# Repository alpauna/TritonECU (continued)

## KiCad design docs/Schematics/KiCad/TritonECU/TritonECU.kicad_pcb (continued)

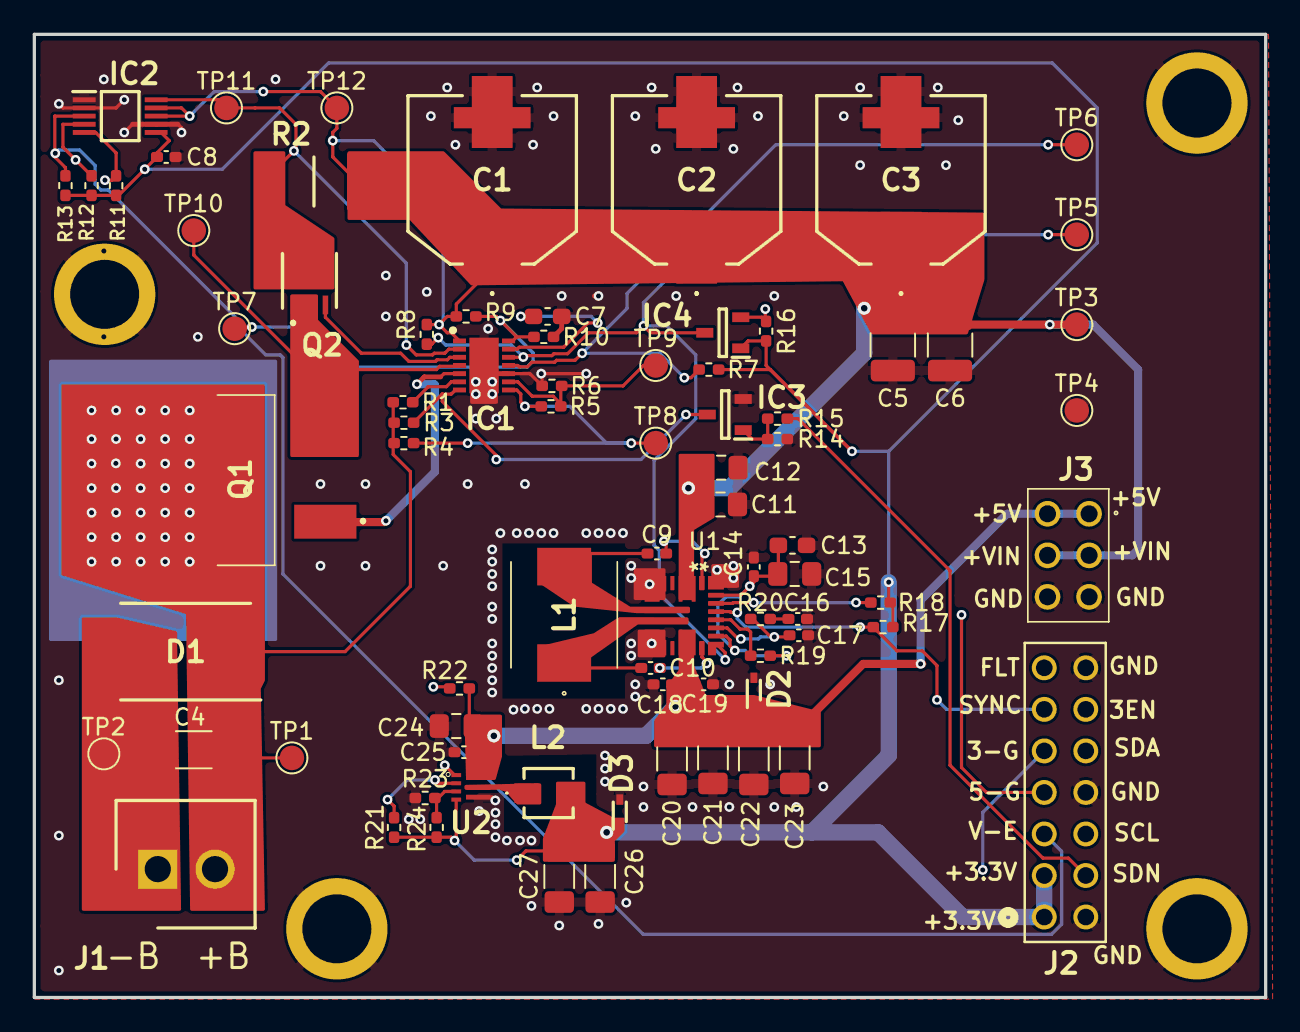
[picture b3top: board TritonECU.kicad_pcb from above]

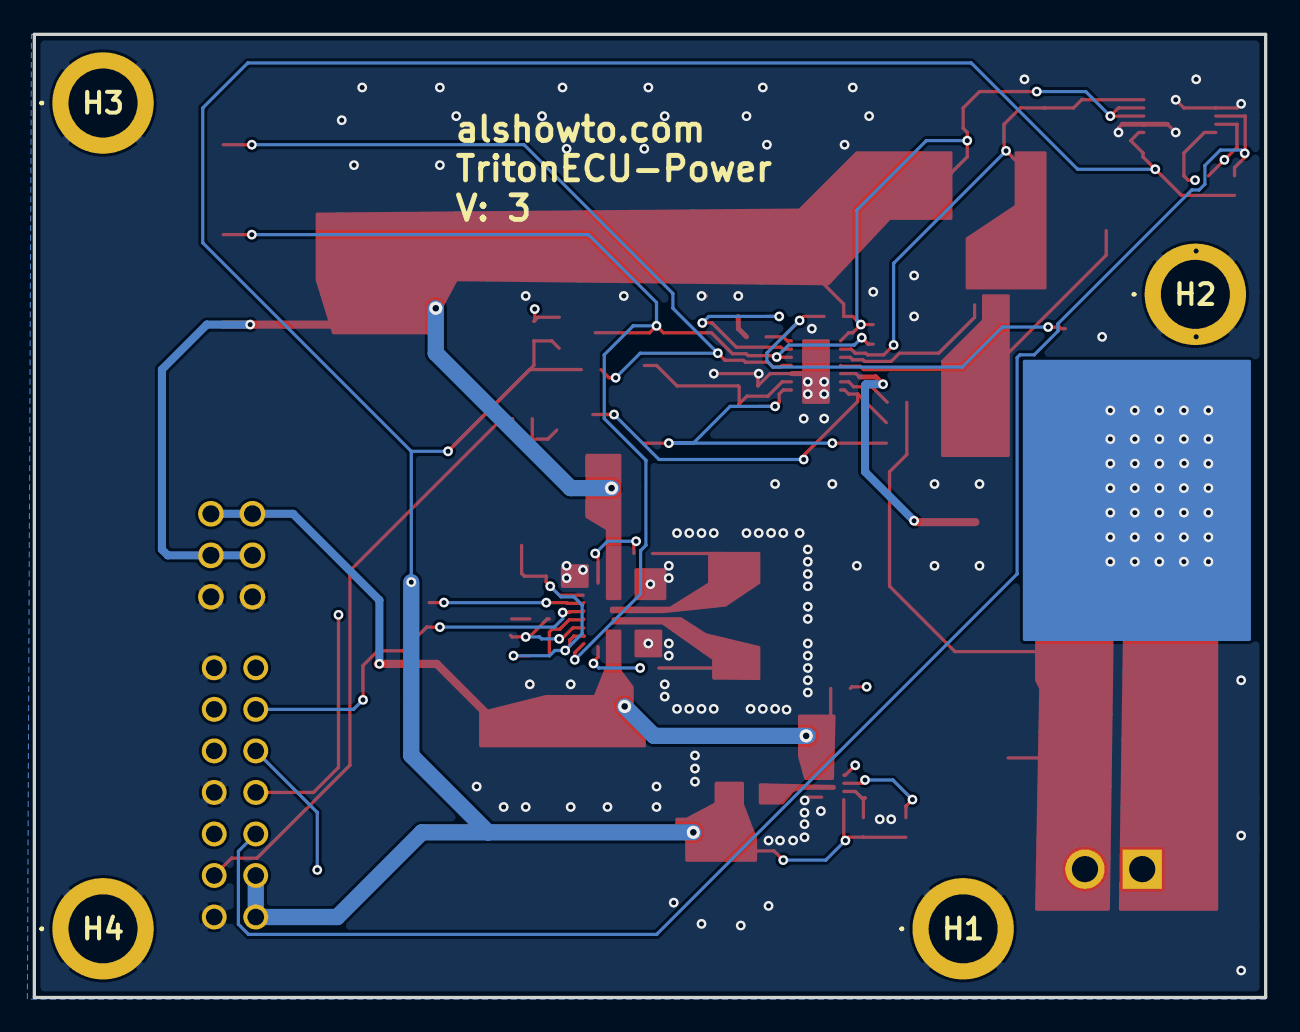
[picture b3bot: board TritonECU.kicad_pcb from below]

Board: 4 copper layers, 75.3 x 58.9 mm, 83 parts (4 on the bottom side), 38 nets.

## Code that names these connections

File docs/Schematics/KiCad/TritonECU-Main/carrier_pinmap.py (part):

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import mcu_pinout as mp

# Standby wake-up pins (DS11532 / RM0410 PWR_CSR2); PI8/PI11 are not on LQFP144
WKUP = {'PA0': 'WKUP1', 'PA2': 'WKUP2', 'PC1': 'WKUP3', 'PC13': 'WKUP4'}
RESERVED = {'PA13': 'SWDIO (STDC14)', 'PA14': 'SWCLK (STDC14)', 'PB3': 'SWO (STDC14)',
            'PD8': 'USART3 TX, ST-Link VCP (STDC14)', 'PD9': 'USART3 RX, ST-Link VCP (STDC14)'}

# Timer modes. 'sched': free-running counter, output compare / input capture at
# arbitrary times. 'pwm': fixed period, the channels share it.
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#   or 'GPIO'.
SIGNALS = [
    # --- ignition: 8 x COP, 74HCT541 #1 -> ISL9V3040. Cylinder numbers.
    ('COIL1', 'PD12', 'TIM4_CH1', False, 'ignition', ''),
    ('COIL2', 'PD13', 'TIM4_CH2', False, 'ignition', ''),
    ('COIL3', 'PD14', 'TIM4_CH3', False, 'ignition', ''),
    ('COIL4', 'PD15', 'TIM4_CH4', False, 'ignition', ''),
    ('COIL5', 'PC6',  'TIM8_CH1', False, 'ignition', ''),
    ('COIL6', 'PC7',  'TIM8_CH2', False, 'ignition', ''),
    ('COIL7', 'PC8',  'TIM8_CH3', False, 'ignition', ''),
    ('COIL8', 'PC9',  'TIM8_CH4', False, 'ignition', ''),
    ('COIL_ARM', 'PD11', 'GPIO', False, 'ignition', '74HCT541 #1 OE1: engine position known, ignition armed'),
    ('WDI', 'PD10', 'GPIO', False, 'ignition', 'TPS3823A-33 kick; its RESET drives OE2 of #1 and OE of #3. NO pull resistor'),
    # --- injection: 8 x ZXMS6005DGQ, direct
    ('INJ1', 'PE9',  'TIM1_CH1', False, 'injection', ''),
    ('INJ2', 'PE11', 'TIM1_CH2', False, 'injection', ''),
    ('INJ3', 'PE13', 'TIM1_CH3', False, 'injection', ''),
    ('INJ4', 'PE14', 'TIM1_CH4', False, 'injection', ''),
    ('INJ5', 'PB4',  'TIM3_CH1', False, 'injection', ''),
    ('INJ6', 'PB5',  'TIM3_CH2', False, 'injection', ''),
    ('INJ7', 'PB14', 'TIM12_CH1', False, 'injection', ''),
    ('INJ8', 'PB15', 'TIM12_CH2', False, 'injection', ''),
    # --- position and speed: 3 x MAX9926
    ('CKP', 'PA15', 'TIM2_CH1', False, 'vr', '36-1 crank; capture on the 32-bit TIM2 timebase'),
    ('CMP', 'PB10', 'TIM2_CH3', False, 'vr', 'cam; capture on TIM2'),
    ('OSS', 'PB6', 'GPIO', True, 'vr', 'output shaft; EXTI + timestamp'),
    ('TSS', 'PB7', 'GPIO', True, 'vr', 'turbine shaft, pin 59; EXTI + timestamp'),
    ('TC_SPEED', 'PE0', 'GPIO', True, 'vr', 'transfer case, pin 7; EXTI + timestamp'),
    # --- ADS8588H, SPI3
    ('ADC_SCK', 'PC10', 'SPI3_SCLK', False, 'adc', ''),
    ('ADC_MISO', 'PC11', 'SPI3_MISO', False, 'adc', 'DOUTA'),
    ('ADC_CS', 'PD2', 'GPIO', False, 'adc', 'software chip select'),
    ('ADC_CONVST', 'PB11', 'TIM2_CH4', False, 'adc', 'CONVSTA+B; compare output on the crank timebase'),
    ('ADC_BUSY', 'PD3', 'GPIO', True, 'adc', 'falling edge = data ready'),
    ('ADC_RESET', 'PD4', 'GPIO', False, 'adc', 'active high; OS0-2, RANGE strapped, FRSTDATA not wired'),
    ('ADC_REF_EN', 'PG10', 'GPIO', False, 'adc', 'MAX6070AAUT25 EN, 10k pulldown: gated off in Standby, always-on-domain.md'),
    # --- internal ADC, analog (3.3 V full scale)
    ('KNOCK', 'PC3', 'ADC1', False, 'analog', '200 kSPS on ADC1, adc-front-end.md'),
    ('DPFE', 'PF3', 'ADC', False, 'analog', ''),
    ('TFT', 'PF4', 'ADC', False, 'analog', 'tft-sensor.md'),
    ('O2_DN1', 'PF6', 'ADC', False, 'analog', 'HO2S #12, buffered'),
    ('O2_DN2', 'PF7', 'ADC', False, 'analog', 'HO2S #22, buffered'),
    ('FP_MON', 'PF10', 'ADC', False, 'analog', 'fuel pump monitor'),
    ('TR3A', 'PC0', 'ADC', False, 'analog', 'three-state, 4R100 270R; 4r100-deltas.md'),
    ('VREF_CS', 'PC1', 'ADC', False, 'analog', 'TPS2H160B current sense, via 4.7k + Schottky'),
    ('VREF_STB', 'PC2', 'ADC', False, 'analog', 'VREF feed short-to-battery divider'),
    ('MUX_OUT', 'PA2', 'ADC', False, 'analog', '74HC4051 COM: drain sense x6 (HO2S x4, EVAP, vent), supply sense 1138, 391'),
    ('MUX_S0', 'PB0', 'GPIO', False, 'analog', '74HC4051 select'),
    ('MUX_S1', 'PB1', 'GPIO', False, 'analog', '74HC4051 select'),
    ('MUX_S2', 'PA7', 'GPIO', False, 'analog', '74HC4051 select'),
    ('O2_BIAS', 'PA4', 'DAC_OUT1', False, 'analog', 'DAC -> 1k -> 455 mV bias node, o2-input-stage.md'),
    # --- solenoids and heaters: 74HCT541 #3 @ 5 V -> NCV8405A x8 (full)
    ('HTR11', 'PG2', 'GPIO', False, 'solenoid', 'HO2S #11 heater, software PWM (ramp, stagger)'),
    ('HTR21', 'PG3', 'GPIO', False, 'solenoid', 'HO2S #21 heater'),
    ('HTR12', 'PG4', 'GPIO', False, 'solenoid', 'HO2S #12 heater'),
    ('HTR22', 'PG5', 'GPIO', False, 'solenoid', 'HO2S #22 heater'),
    ('VENT', 'PG6', 'GPIO', False, 'solenoid', 'canister vent, pin 67'),
    ('IMCC', 'PG7', 'GPIO', False, 'solenoid', 'pin 46'),
    ('SSA', 'PG8', 'GPIO', False, 'solenoid', 'pin 6 (5.4L; 27 is the 4.6L pin)'),
    ('SSB', 'PB12', 'GPIO', False, 'solenoid', 'pin 11 (5.4L; 1 is the 4.6L pin)'),
    # --- PWM loads: 74HCT541 #2 @ 5 V
    ('EVAP', 'PE5', 'TIM9_CH1', False, 'pwm', 'purge, pin 56; shares TIM9 period with EGR'),
    ('EGR', 'PE6', 'TIM9_CH2', False, 'pwm', 'EVR, pin 47'),
    ('EPC', 'PB8', 'TIM10_CH1', False, 'pwm', 'NCV8408B, pin 81, >= 200 Hz, own timer'),
    ('TCC', 'PB9', 'TIM11_CH1', False, 'pwm', 'pin 54, own timer'),
    ('IAC', 'PF8', 'TIM13_CH1', False, 'pwm', 'pin 83, own timer'),
    ('VSS_OUT', 'PA3', 'TIM5_CH4', False, 'pwm', 'pin 68 open drain via NCV8405A #13; frequency by compare toggle'),
    ('CCS', 'PB13', 'GPIO', False, 'pwm', 'coast clutch, pin 20, #2 ch7'),
    ('PWM_OE', 'PA8', 'GPIO', False, 'pwm', '74HCT541 #2 OE, software-releasable'),
    # --- relays: TBD62083AFNG, direct at 3.3 V
    ('FPUMP', 'PE7', 'GPIO', False, 'relay', ''),
    ('FAN1', 'PE12', 'GPIO', False, 'relay', ''),
    ('FAN2', 'PE15', 'GPIO', False, 'relay', ''),
    ('ACC', 'PG0', 'GPIO', False, 'relay', 'A/C clutch'),
    # --- switch inputs, conditioned
    ('TR1', 'PF11', 'GPIO', True, 'input', 'pin 34'),
    ('TR2', 'PF12', 'GPIO', True, 'input', 'pin 49'),
    ('TR4', 'PF14', 'GPIO', True, 'input', 'pin 50'),
    ('BRAKE', 'PF15', 'GPIO', True, 'input', ''),
    ('ACP', 'PE10', 'GPIO', True, 'input', 'A/C pressure'),
    ('4X4L', 'PE8', 'GPIO', True, 'input', '4x4 low indicator switch, pin 14 (findings sec.14)'),
    ('TCS', 'PE1', 'GPIO', False, 'input', 'O/D cancel switch, pin 29; polled, all EXTI lines are taken'),
    # --- VREF: TPS2H160B-Q1, DIAG_EN tied high
    ('VREF_EN', 'PB2', 'GPIO', False, 'vref', ''),
    ('VREF_IN1', 'PF13', 'GPIO', False, 'vref', ''),
    ('VREF_IN2', 'PC4', 'GPIO', False, 'vref', ''),
    ('VREF_SEL', 'PC5', 'GPIO', False, 'vref', ''),
    ('VREF_FAULT', 'PF9', 'GPIO', True, 'vref', ''),
    # --- SCP / J1850 PWM: DRV8837 + TLV7031
    ('J1850_TXP', 'PG13', 'GPIO', False, 'j1850', 'same port as TXN: one BSRR write'),
    ('J1850_TXN', 'PG14', 'GPIO', False, 'j1850', ''),
    ('J1850_NSLEEP', 'PG15', 'GPIO', False, 'j1850', ''),
    ('J1850_RX', 'PA1', 'TIM2_CH2', False, 'j1850', 'capture on the TIM2 timebase'),
    # --- CAN: TJA1042T/3
    ('CAN_RX', 'PD0', 'CAN1_CAN_RD', False, 'can', ''),
    ('CAN_TX', 'PD1', 'CAN1_CAN_TD', False, 'can', ''),
    ('CAN_STB', 'PD5', 'GPIO', False, 'can', 'not strapped: standby is what reaches 20 uA'),
    ('CAN_RX_WAKE', 'PA0', 'WKUP1', False, 'can', 'SAME NET as CAN_RX: Standby wakes only on a WKUP pin'),
    # --- wake, power board, I2C
    ('IGN_WAKE', 'PC13', 'WKUP4', True, 'power', 'key-on sense, conditioned; also key-off detect'),
    ('SW_RAIL_EN', 'PG12', 'GPIO', False, 'power', 'TPS22917 x2: +5V_SW, +3.3V_SW for the running-only loads; 100k down'),
    ('I2C_SDA', 'PF0', 'I2C2_SDA', False, 'power', 'power board, INA238, baro'),
    ('I2C_SCL', 'PF1', 'I2C2_SCL', False, 'power', ''),
    ('M_SYNC', 'PE3', 'GPIO', False, 'power', 'MAX25239 SYNC; 10k pull-down on the power board'),
    ('U_SHDN', 'PF2', 'GPIO', False, 'power', ''),
    ('ENOUT', 'PE2', 'GPIO', True, 'power', '3.3_ENOUT, LTC4364 enable'),
    ('FLT', 'PE4', 'GPIO', True, 'power', ''),
    ('VIN_ALERT', 'PF5', 'GPIO', True, 'power', ''),
    ('5_GOOD', 'PG1', 'GPIO', True, 'power', ''),
    # --- storage, USB
    ('SD_CK', 'PD6', 'SDMMC2_SD_CK', False, 'storage', '1-bit'),
    ('SD_CMD', 'PD7', 'SDMMC2_SD_CMD', False, 'storage', ''),
    ('SD_D0', 'PG9', 'SDMMC2_SD_DATA0', False, 'storage', ''),
    ('SD_PWR_EN', 'PG11', 'GPIO', False, 'storage', 'TPS22917 ON, 100k pulldown: the card is off when parked (3.3 V is always on)'),
    ('USB_DM', 'PA11', 'USB_OTG_FS_USB_OTG_FS', False, 'usb', 'tuning path'),
    ('USB_DP', 'PA12', 'USB_OTG_FS_USB_OTG_FS', False, 'usb', ''),
    ('USB_VBUS', 'PA9', 'USB_OTG_FS_USB_OTG_FS', False, 'usb', 'via divider'),
    # --- test header, 3.3 V, stops at the header
    ('TACH', 'PA5', 'GPIO', False, 'test', 'software square wave'),
    ('SPEED', 'PA6', 'GPIO', False, 'test', 'software square wave'),
]


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
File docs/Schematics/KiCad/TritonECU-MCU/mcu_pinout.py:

#!/usr/bin/env python3
"""TritonECU MCU module: the STM32F767ZIT6 (LQFP144) on a 44 x 44 mm board that
replaces the Nucleo-144 on the carrier. Single source of truth for the module's
four edge headers; the carrier footprint (TritonECU-Main/gen_floorplan.py) and
the module's own PCB both read it.

Headers: four 2x18, 1.27 mm pitch, one per side of the QFP, both SURFACE
MOUNT. Samtec FTSH-118-02-L-DV-A on the module bottom mates with
FLE-118-01-G-DV-K-TR on the carrier top at 7.47 mm (Samtec's FTSH-02 / FLE-01
mated set), so the M3 standoffs are 7.47 mm too. Pad geometry is from the
vendor footprints the user imported via Component Search Engine and impart on
2026-10-17 (Samacsys FTSH-118-XX-YYY-DV-A and FLE11801GDVKTR).
module_pins() gives the CONTACT positions, which is where the pins mate.
smt_pads() gives the solder pads, splayed outward from each contact row. Each header carries the pins of the QFP side it
faces, in package order, so the module escape is a straight fan-out:

  A  left    package 1-36,    top -> bottom
  B  bottom  package 37-72,   left -> right
  C  right   package 73-108,  bottom -> top
  D  top     package 109-144, right -> left

Slot k (0..35) is position k // 2 along the header; even slots are the inner
row (nearer the QFP), odd slots the outer. Pad name = side letter + (k + 1),
so odd pad numbers are the inner row.

Mapping rules, applied in package order:
  Pxx           -> the port pin, broken out   (except the crystal pins below)
  VSS, VSSA     -> GND
  VDD, VDDUSB, VDDSDMMC -> +3.3V (fed by the carrier; the module has no regulator)
  NRST, VBAT, BOOT0 -> broken out (carrier watchdog drives NRST; carrier decides VBAT)
  PC14/PC15 (LSE 32.768 kHz), PH0/PH1 (HSE 8 MHz) -> crystals on the module
  VDDA, VREF+   -> on the module: ferrite from VDD, VREF+ tied to VDDA
  VCAP_1/2      -> 2.2 uF each on the module
  PDR_ON        -> VDD on the module (internal supervisor on)
Unused slots are filled with GND, alternately at the start and end of the header.

Usage:  python3 mcu_pinout.py           prints the pinout as a markdown table
"""

LQFP144 = """
    PE2 PE3 PE4 PE5 PE6 VBAT PC13 PC14 PC15 PF0 PF1 PF2
    PF3 PF4 PF5 VSS VDD PF6 PF7 PF8 PF9 PF10 PH0 PH1
    NRST PC0 PC1 PC2 PC3 VDD VSSA VREF+ VDDA PA0 PA1 PA2
    PA3 VSS VDD PA4 PA5 PA6 PA7 PC4 PC5 PB0 PB1 PB2
    PF11 PF12 VSS VDD PF13 PF14 PF15 PG0 PG1 PE7 PE8 PE9
    VSS VDD PE10 PE11 PE12 PE13 PE14 PE15 PB10 PB11 VCAP_1 VDD
    PB12 PB13 PB14 PB15 PD8 PD9 PD10 PD11 PD12 PD13 VSS VDD
    PD14 PD15 PG2 PG3 PG4 PG5 PG6 PG7 PG8 VSS VDDUSB PC6
    PC7 PC8 PC9 PA8 PA9 PA10 PA11 PA12 PA13 VCAP_2 VSS VDD
    PA14 PA15 PC10 PC11 PC12 PD0 PD1 PD2 PD3 PD4 PD5 VSS
    VDDSDMMC PD6 PD7 PG9 PG10 PG11 PG12 PG13 PG14 VSS VDD PG15
    PB3 PB4 PB5 PB6 PB7 BOOT0 PB8 PB9 PE0 PE1 PDR_ON VDD
""".split()   # STM32F767ZITx, package pin 1..144 (KiCad MCU_ST_STM32F7, = DS11532)
assert len(LQFP144) == 144

ON_MODULE = {'PC14', 'PC15', 'PH0', 'PH1', 'VDDA', 'VREF+', 'VCAP_1', 'VCAP_2', 'PDR_ON'}
TO_NET = {'VSS': 'GND', 'VSSA': 'GND', 'VDD': '+3.3V', 'VDDUSB': '+3.3V', 'VDDSDMMC': '+3.3V'}

BOARD = 46.0          # module outline, square, centred on the QFP (44 -> 46 for the Ø9.4 spacer pads)
STANDOFF = 7.47       # board-to-board = the FTSH-02 / FLE-01 mated height:
                      #   module: Wurth 9774050982R 5.0 mm SMT spacer on its bottom (Ø4.5 bore)
                      #   carrier: PEM SMTSO-M3-2ET 2.0 mm SMT M3 standoff on its top
                      #   + one 0.5 mm M3 washer (DIN 433) between them = 7.5 mm
                      #   (no 2.5 mm SMTSO exists; 7.0 would over-press the connectors)
SPACER_MPN = '9774050982R'
STANDOFF_MPN = 'SMTSO-M3-2ET'
HEADER_MPN = 'FTSH-118-02-L-DV-A'   # module side: Samtec 2x18 1.27 mm header, SMT, -A board alignment pins
SOCKET_MPN = 'FLE-118-01-G-DV-K-TR'   # carrier side: Samtec 2x18 1.27 mm socket strip, SMT, no alignment pins
STACK_NOTE = '7.47 mm mated (Samtec FTSH-xx-02 + FLE-xx-01)'
SLOTS = 36            # 2 x 18
PITCH = 1.27
ROW_IN = 16.5         # inner-row contact distance from the module centre; FTSH courtyards (+-12.63 along) clear at the corners
ROW_OUT = ROW_IN + PITCH
# M3 standoffs. H1 (the QFP pin-1 corner) sits 0.7 mm further IN on each axis so
# the module only fits one way round (inward: the spacer's Ø9.4 pad would reach
# the board edge if it moved out): the four headers are identical and the
# FLE socket gives no polarization, and any 90/180/270 rotation would put
# +3.3V and GND on signal pins.
HOLES = [(-16.8, -16.8), (17.5, -17.5), (17.5, 17.5), (-17.5, 17.5)]
HOLE_DRILL, HOLE_PAD = 4.3, 6.45  # carrier: PEM SMTSO-M3-2ET land (Samacsys SMTSOM32ET; PEM: hole 4.22, pad >= 6.2)
# vendor SMT geometry, per header, relative to the header centre:
#   pad = (width along the header, length across), off = pad-centre distance from the
#   header centreline, align = Ø of the two -A alignment holes (NPTH) at +-align_x on
#   the centreline (None: no alignment pins), body = half length, half width
# FTSH: Samacsys has 0.74 x 2.79 at 2.035, which leaves 0.18 mm from the -A holes to
# the neighbouring pads. The inner 0.1 mm is trimmed (outer end unchanged, still
# ~1 mm under the body) to meet the 0.25 mm hole clearance rule.
FTSH = dict(pad=(0.74, 2.69), off=2.085, align=1.02, align_x=10.16, body=(11.43, 1.715))   # module, bottom
FLE = dict(pad=(0.74, 1.675), off=1.843, align=None, body=(11.43, 2.127))   # carrier, top

SIDES = 'ABCD'


def side_signals(side):
    """Signal list for one header, in slot order."""
    i = SIDES.index(side)
    sig = []
    for name in LQFP144[i * 36:(i + 1) * 36]:
        if name in ON_MODULE:
            continue
        sig.append((TO_NET.get(name, name), LQFP144.index(name) + 1 if name not in TO_NET else None))
    assert len(sig) <= SLOTS, (side, len(sig))
    front = True
    while len(sig) < SLOTS:
        if front: sig.insert(0, ('GND', None))
        else: sig.append(('GND', None))
        front = not front
    return sig


def slot_xy(side, k):
    """Pad centre relative to the module centre, KiCad axes (y down), top view."""
    along = (k // 2 - (SLOTS // 2 - 1) / 2) * PITCH
    d = ROW_IN if k % 2 == 0 else ROW_OUT
    if side == 'A': return (-d, along)
    if side == 'B': return (along, d)
    if side == 'C': return (d, -along)
    return (-along, -d)


def header_frame(side):
    """(centre, along unit vector, outward unit vector) of a header, module coords."""
    c = ROW_IN + PITCH / 2
    return {'A': ((-c, 0), (0, 1), (-1, 0)), 'B': ((0, c), (1, 0), (0, 1)),
            'C': ((c, 0), (0, -1), (1, 0)), 'D': ((0, -c), (-1, 0), (0, -1))}[side]


def smt_pads(spec):
    """[(pad, x, y, size_x, size_y, net)]: solder pads for TFM or SFM, module coords."""
    out = []
    for pad, x, y, net in module_pins():
        (cx, cy), _, (ox, oy) = header_frame(pad[0])
        k = int(pad[1:]) - 1
        sgn = -1 if k % 2 == 0 else 1          # odd pads = inner row
        across = (cx + ox * sgn * spec['off'], cy + oy * sgn * spec['off'])
        px = across[0] if ox else x            # keep the along position of the contact
        py = across[1] if oy else y
        w, l = spec['pad']
        sx, sy = (l, w) if ox else (w, l)
        out.append((pad, round(px, 4), round(py, 4), sx, sy, net))
    return out


def align_holes(spec):
    """[(x, y, dia)]: two -A alignment holes per header (none if the part has no -A)."""
    out = []
    if not spec.get('align'):
        return out
    for s in SIDES:
        (cx, cy), (ax, ay), _ = header_frame(s)
        for t in (-1, 1):
            out.append((round(cx + ax * t * spec['align_x'], 4), round(cy + ay * t * spec['align_x'], 4), spec['align']))
    return out


def module_pins():
    """[(pad, x, y, net)] for all 144 header pins."""
    out = []
    for s in SIDES:
        for k, (net, _) in enumerate(side_signals(s)):
            x, y = slot_xy(s, k)
            out.append((f'{s}{k + 1}', round(x, 4), round(y, 4), net))
    return out


def check():
    pins = module_pins()
    ports = [n for _, _, _, n in pins if n.startswith('P')]
    assert len(ports) == len(set(ports)), 'port pin on two headers'
    want = {n for n in LQFP144 if n.startswith('P') and n not in ON_MODULE}
    assert set(ports) == want, want ^ set(ports)
    for n in ('NRST', 'VBAT', 'BOOT0'):
        assert sum(p[3] == n for p in pins) == 1, n
    return pins


if __name__ == '__main__':
    pins = check()
    print('| pad | net | pad | net |\n|---|---|---|---|')
    for s in SIDES:
        sp = [p for p in pins if p[0][0] == s]
        for a, b in zip(sp[0::2], sp[1::2]):
            print(f'| {a[0]} | {a[3]} | {b[0]} | {b[3]} |')
    io = sum(p[3].startswith('P') for p in pins)
    print(f'\n{io} port pins, {sum(p[3] == "GND" for p in pins)} GND, '
          f'{sum(p[3] == "+3.3V" for p in pins)} +3.3V, plus NRST, VBAT, BOOT0')

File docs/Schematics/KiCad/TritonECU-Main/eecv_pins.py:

#!/usr/bin/env python3
"""EEC-V 104-pin connector (J1): which carrier net lands on which pin, for the
1999 F-150 5.4L. The connector-side twin of carrier_pinmap.py.

Sources, in order of authority:
  1. Ford's diagrams, as read in 1999-Ford-F150-4wd-5.42v/schematic-findings.md.
     Their legend: `*` = 5.4L, `**` = 4.2L/4.6L. "SSA -> PCM 27 (*6)" therefore
     means pin 6 on THIS truck; 27 is the 4.6L pin, and on the 5.4L pin 27 is
     coil 5.
  2. eec-v-pinout.md, the '99 F150 column (MegaSquirt PNP sheet).
  3. Design documents for pins this ECU adds (freewheel returns, fan 2).

Checked: no pin carries two nets, every pin is 1-104, the grounds and VPWR are
the 5.4L's (pin 24 is the 4.6L ground, not used).

Usage:  python3 eecv_pins.py        check, and list the nets by connector position
"""
import re, os

# pin: (net, what, source)
PINS = {
    # --- power and returns
    71: ('VPWR', 'key-switched power, 361 RD', 'pinout + findings sec.17'),
    97: ('VPWR', 'key-switched power, 361 RD', 'pinout + findings sec.17'),
    3: ('GND', 'power ground, 570 BK/WH (the 5.4L fourth ground is *3)', 'findings'),
    51: ('GND', 'power ground', 'pinout'),
    77: ('GND', 'power ground', 'pinout'),
    103: ('GND', 'power ground', 'pinout'),
    55: ('VBAT_SENSE', 'battery voltage sense, 729 RD/WH, KAM feed', 'findings sec.19'),
    90: ('VREF', '5 V sensor reference', 'pinout'),
    91: ('SIGRTN', 'sensor return, 359', 'schematic-ecu-v1 sec.14a'),
    36: ('MAF_RTN', 'MAF return, Kelvin sense (not AGND at the connector)', 'schematic-ecu-v1 sec.14a'),
    48: ('FW_391', 'circuit 391 brought in as a freewheel return', 'schematic-ecu-v1 sec.12'),
    82: ('FW_1138', 'circuit 1138 brought in as a freewheel return (TCC, EPC, SSA, SSB)', 'findings sec.5'),
    25: ('CMP_SHIELD', 'CMP shield drain, 567 LB/YE', 'pinout + findings'),
    # --- ignition, COP. Coil n = cylinder n
    26: ('COIL1_OUT', 'coil 1', 'pinout'), 104: ('COIL2_OUT', 'coil 2', 'pinout'),
    52: ('COIL3_OUT', 'coil 3', 'pinout'), 53: ('COIL4_OUT', 'coil 4', 'pinout'),
    27: ('COIL5_OUT', 'coil 5', 'pinout'), 1: ('COIL6_OUT', 'coil 6', 'pinout'),
    78: ('COIL7_OUT', 'coil 7', 'pinout'), 79: ('COIL8_OUT', 'coil 8', 'pinout'),
    # --- injection
    75: ('INJ1_OUT', 'injector 1', 'pinout'), 101: ('INJ2_OUT', 'injector 2', 'pinout'),
    74: ('INJ3_OUT', 'injector 3', 'pinout'), 100: ('INJ4_OUT', 'injector 4', 'pinout'),
    73: ('INJ5_OUT', 'injector 5', 'pinout'), 99: ('INJ6_OUT', 'injector 6', 'pinout'),
    72: ('INJ7_OUT', 'injector 7', 'pinout'), 98: ('INJ8_OUT', 'injector 8', 'pinout'),
    # --- solenoids and heaters (74HCT541 #3 group)
    93: ('HTR11_OUT', 'HO2S 11 heater (RF/bank 1 upstream)', 'pinout'),
    94: ('HTR21_OUT', 'HO2S 21 heater (LF)', 'pinout'),
    95: ('HTR12_OUT', 'HO2S 12 heater (RR)', 'pinout'),
    96: ('HTR22_OUT', 'HO2S 22 heater (LR)', 'pinout'),
    67: ('VENT_OUT', 'canister vent', 'findings'),
    46: ('IMCC_OUT', 'intake manifold communication control', 'pinout'),
    6: ('SSA_OUT', 'shift solenoid A, 237 OG/YE (*6 = 5.4L)', 'findings sec.5'),
    11: ('SSB_OUT', 'shift solenoid B, 315 VT/OG (*11 = 5.4L)', 'findings sec.5'),
    # --- PWM loads (74HCT541 #2 group)
    56: ('EVAP_OUT', 'canister purge', 'pinout'),
    47: ('EGR_OUT', 'EGR vacuum regulator', 'pinout'),
    54: ('TCC_OUT', 'torque converter clutch', 'findings sec.5'),
    81: ('EPC_OUT', 'electronic pressure control', 'findings sec.5'),
    83: ('IAC_OUT', 'idle air control', 'pinout'),
    68: ('VSS_OUT_PIN', 'road speed out, 679 GY/BK, open drain', 'findings'),
    20: ('CCS_OUT', 'coast clutch, 4R100 only (free on the 4R70W)', 'pinout'),
    # --- relays
    80: ('FPUMP_OUT', 'fuel pump relay', 'pinout'),
    19: ('FAN1_OUT', 'cooling fan 1 relay', 'pinout, cooling-fans.md'),
    18: ('FAN2_OUT', 'cooling fan 2 relay', 'pinout, cooling-fans.md'),
    69: ('ACC_OUT', 'A/C WOT cut-out relay, 331 PK/YE', 'findings sec.8'),
    # --- position and speed (to the VR board)
    21: ('CKP_P', 'crank +', 'pinout'), 22: ('CKP_N', 'crank -', 'pinout'),
    85: ('CMP_IN', 'cam, VR single-ended', 'pinout'),
    84: ('OSS_IN', 'output shaft speed', 'findings sec.7'),
    59: ('TSS_IN', 'turbine shaft speed', 'pinout'),
    7: ('TC_SPEED_IN', 'transfer case speed, 1496 PK', 'findings sec.7'),
    # --- analog sensors (ADS8588H or the internal ADC)
    88: ('MAF_IN', 'MAF', 'pinout'), 89: ('TPS_IN', 'throttle position', 'pinout'),
    39: ('IAT_IN', 'intake air temperature', 'pinout'),
    66: ('CHT_IN', 'cylinder head temperature', 'pinout'),
    65: ('DPFE_IN', 'EGR delta-pressure', 'pinout'),
    37: ('TFT_IN', 'transmission fluid temperature', 'pinout'),
    40: ('FP_MON_IN', 'fuel pump monitor', 'pinout'),
    60: ('O2_11_IN', 'HO2S 11 (RF upstream)', 'pinout'),
    87: ('O2_21_IN', 'HO2S 21 (LF upstream)', 'pinout'),
    35: ('O2_12_IN', 'HO2S 12 (RR downstream)', 'pinout'),
    61: ('O2_22_IN', 'HO2S 22 (LR downstream)', 'pinout'),
    57: ('KNOCK_IN', 'knock sensor', 'pinout'),
    32: ('KNOCK_RTN', 'knock sensor, second wire (two-wire piezo)', 'pinout, knock-front-end.md'),
    # --- switches
    34: ('TR1_IN', 'trans range 1', 'pinout'), 49: ('TR2_IN', 'trans range 2', 'pinout'),
    64: ('TR3A_IN', 'trans range 3A / start in P or N, 199 LB/YE', 'findings sec.21'),
    50: ('TR4_IN', 'trans range 4', 'pinout'),
    92: ('BRAKE_IN', 'brake pedal position', 'pinout'),
    41: ('ACP_IN', 'A/C cycling pressure switch, 347 BK/YE', 'findings sec.8'),
    29: ('TCS_IN', 'O/D cancel switch', 'pinout'),
    14: ('4X4L_IN', '4x4 low indicator switch, 784 LB/BK (C189)', 'findings sec.14-15'),
    # --- bus
    15: ('SCP_N', 'SCP- 915 PNK/LT BLU', 'pinout'), 16: ('SCP_P', 'SCP+ 914 TAN/ORG', 'pinout'),
    # private CAN to the dash display: terminals ADDED in two empty cavities beside SCP
    42: ('CAN_H', 'CAN high, added terminal (unused cavity)', 'can-bus.md'),
    43: ('CAN_L', 'CAN low, added terminal (unused cavity)', 'can-bus.md'),
}

# Deliberately unconnected, with the reason
NOT_CONNECTED = {
    24: '4.2L/4.6L ground pin; not wired on the 5.4L',
    13: 'FEPS / DLC 13: 18 V programming, leave open on a 3.3 V system',
    12: 'trans control indicator lamp: dash is on SCP',
    62: 'fuel tank pressure: not fitted',
    63: 'fuel pressure: future',
    38: 'MS sheet ECT jumper: this truck uses CHT on 66',
}

# signals carrier_pinmap.py has but the connector does not carry, and why
OFF_CONNECTOR = {'TACH': 'test header only', 'SPEED': 'test header only'}


def pad_positions():
    t = open(os.path.join(os.path.dirname(os.path.abspath(__file__)), 'TritonECU-Main.pretty', 'EECV_104.kicad_mod')).read()
    return {int(n): (float(x), float(y)) for n, x, y in re.findall(r'\(pad "(\d+)" \w+ \w+ \(at ([-\d.]+) ([-\d.]+)', t)}


def check():
    errors = []
    for p in PINS:
        if not 1 <= p <= 104:
            errors.append(f'pin {p} out of range')
        if p in NOT_CONNECTED:
            errors.append(f'pin {p} is both used and not connected')
    if 24 in PINS:
        errors.append('pin 24 is the 4.6L ground')
    for coil, ss in ((27, 6), (1, 11)):
        if not PINS[coil][0].startswith('COIL') or not PINS[ss][0].startswith('SS'):
            errors.append(f'pins {coil}/{ss}: coil/shift-solenoid swap (4.6L numbering)')
    return errors


if __name__ == '__main__':
    errs = check()
    for e in errs:
        print('ERROR', e)
    pads = pad_positions()
    groups = {}
    for p, (net, *_ ) in PINS.items():
        g = re.sub(r'\d*_?(OUT|IN|P|N|RTN|PIN)?$', '', net) or net
        groups.setdefault(g, []).append(p)
    print(f'{len(PINS)} pins used, {len(NOT_CONNECTED)} deliberately open, {104 - len(PINS) - len(NOT_CONNECTED)} free')
    for g, ps in sorted(groups.items(), key=lambda kv: min(pads[p][0] for p in kv[1])):
        xs = [pads[p][0] for p in ps]
        print(f'  {g:10s} x {min(xs):6.1f} .. {max(xs):6.1f}   pins {sorted(ps)}')
    raise SystemExit(1 if errs else 0)
